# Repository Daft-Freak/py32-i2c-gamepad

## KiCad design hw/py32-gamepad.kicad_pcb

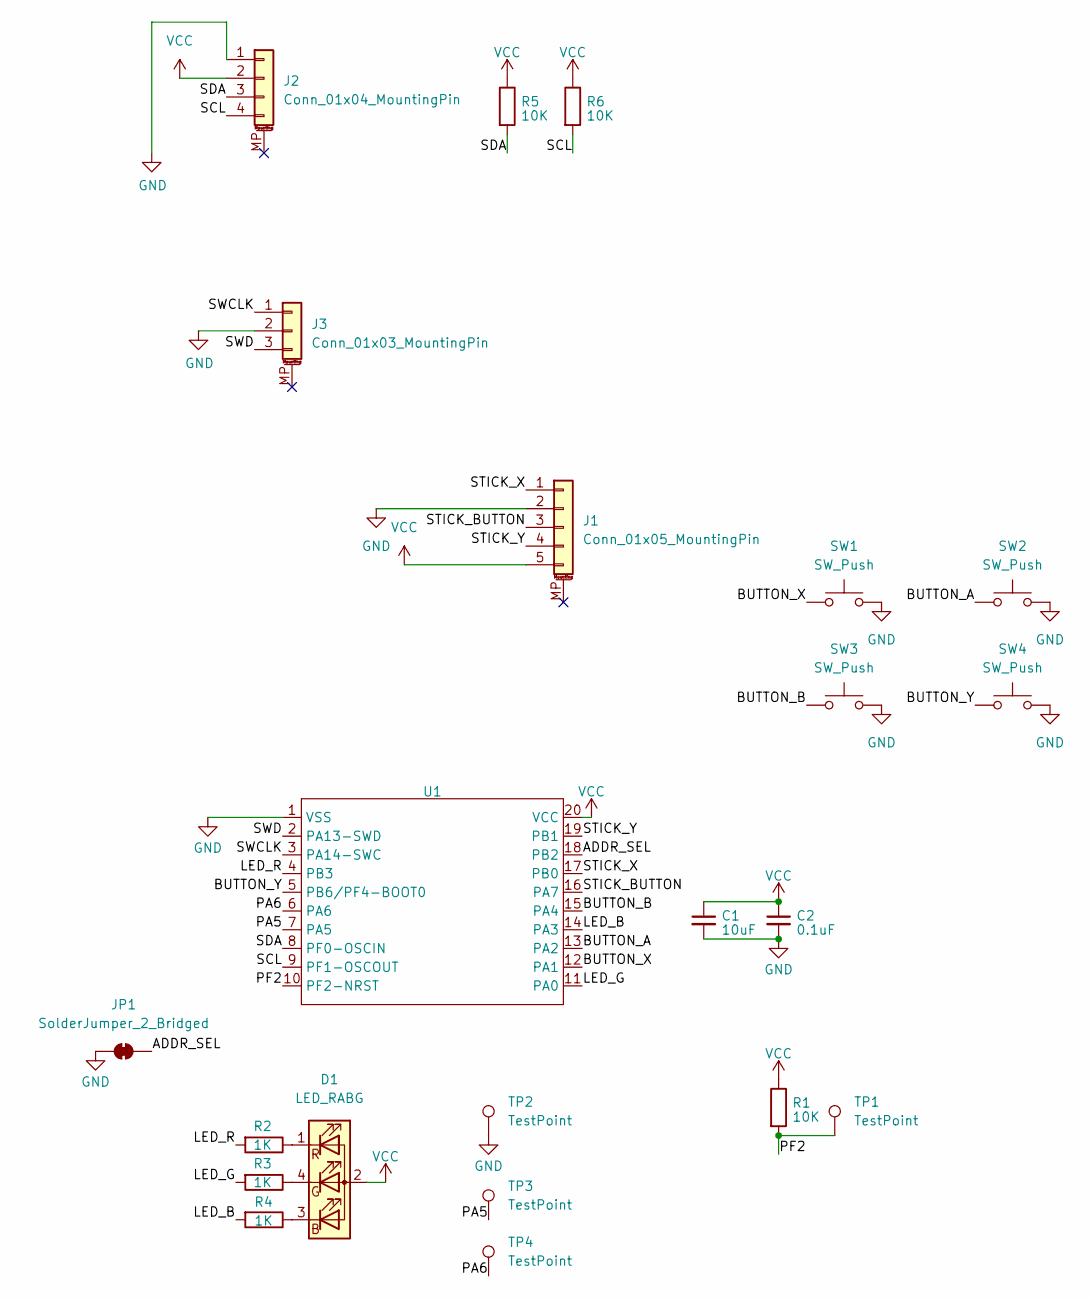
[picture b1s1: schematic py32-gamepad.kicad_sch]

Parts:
C1: 10uF; C_0603_1608Metric
C2: 0.1uF; C_0402_1005Metric
D1: LED_RABG; LED_0606
J1: Conn_01x05_MountingPin; HCTL_HC-FPC-05-09-5RLTAG-00_1x05-1MP_P0.50mm_Horizontal
J2: Conn_01x04_MountingPin; JST_SH_SM04B-SRSS-TB_1x04-1MP_P1.00mm_Horizontal
J3: Conn_01x03_MountingPin; JST_SH_SM03B-SRSS-TB_1x03-1MP_P1.00mm_Horizontal
JP1: SolderJumper_2_Bridged; SolderJumper-2_P1.3mm_Bridged_RoundedPad1.0x1.5mm
R1, R5, R6: 10K; R_0402_1005Metric
R2, R3, R4: 1K; R_0402_1005Metric
SW1, SW2, SW3, SW4: SW_Push; SW_Push_1P1T_NO_GT-TC155x
TP1, TP2, TP3, TP4: TestPoint; TestPoint_Pad_1.0x1.0mm
U1: TSSOP-20_4.4x6.5mm_P0.65mm

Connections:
/ADDR_SEL: JP1.2 (B), U1.18 (PB2)
/BUTTON_A: SW2.1, U1.13 (PA2)
/BUTTON_B: SW3.1, U1.15 (PA4)
/BUTTON_X: SW1.1, U1.12 (PA1)
/BUTTON_Y: SW4.1, U1.5 (PB6/PF4-BOOT0)
/LED_B: R4.2, U1.14 (PA3)
/LED_G: R3.2, U1.11 (PA0)
/LED_R: R2.2, U1.4 (PB3)
/PA5: TP3.1, U1.7 (PA5)
/PA6: TP4.1, U1.6 (PA6)
/PF2: R1.2, TP1.1, U1.10 (PF2-NRST)
/SCL: J2.4, R6.2, U1.9 (PF1-OSCOUT)
/SDA: J2.3, R5.2, U1.8 (PF0-OSCIN)
/STICK_BUTTON: J1.3, U1.16 (PA7)
/STICK_X: J1.1, U1.17 (PB0)
/STICK_Y: J1.4, U1.19 (PB1)
/SWCLK: J3.1, U1.3 (PA14-SWC)
/SWD: J3.3, U1.2 (PA13-SWD)
GND: C1.2, C2.2, J1.2, J2.1, J3.2, JP1.1 (A), SW1.2, SW2.2, SW3.2, SW4.2, TP2.1, U1.1 (VSS)
unnamed: D1.3 (BK), R4.1
unnamed: D1.4 (GK), R3.1
unnamed: D1.1 (RK), R2.1
VCC: C1.1, C2.1, D1.2 (A), J1.5, J2.2, R1.1, R5.1, R6.1, U1.20 (VCC)

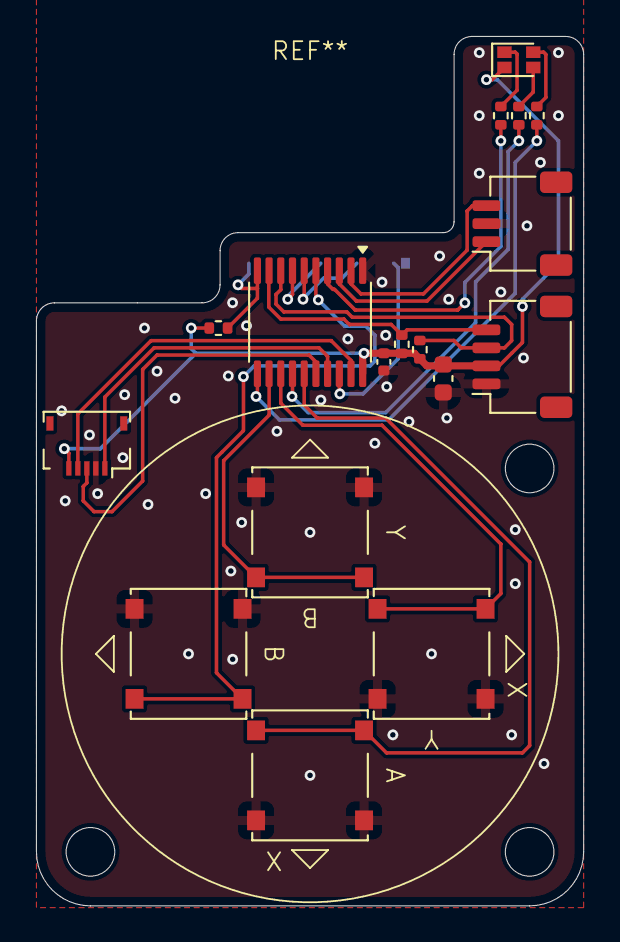
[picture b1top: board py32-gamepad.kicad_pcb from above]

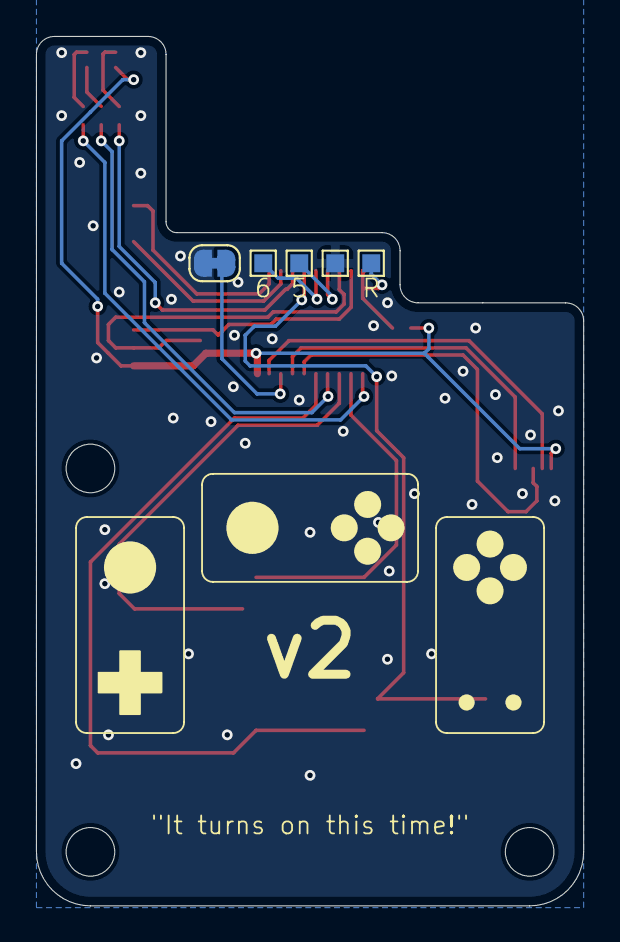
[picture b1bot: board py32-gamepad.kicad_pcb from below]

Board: 2 copper layers, 30.4 x 48.3 mm, 22 parts (5 on the bottom side), 23 nets.

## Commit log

2024-11-14 Initial CMake setup
    It compiles, but we're missing the startup code. startup and linker script taken from https://github.com/IOsetting/py32f0-template
2024-11-14 Import minimal ARM CMSIS headers
    https://github.com/ARM-software/CMSIS_6 v6.1.0
2024-11-14 Import (minimal) puya CMSIC pack
    From https://www.puyasemi.com/uploadfiles/Puya.PY32F0xx_DFP.1.2.2.pack
2024-11-14 Build system init code
2024-11-14 Debug setup
    That was easier than expected
2024-11-14 Setup clocks and test uart
2024-11-15 Init systick and add a very basic delay func
2024-11-15 uart printf helper
2024-11-15 ADC setup
2024-11-15 Less adc printing
2024-11-15 Big pile of gpio helpers
    Also, use the right port for the analog pins
2024-11-15 Some more inputs
2024-11-16 I2C slave setup
    Okay, that's the basic idea working!
2024-12-17 Update for PCB
    Mostly disabling UART and pulling up a few more pins
2024-12-17 Inputs are inputs
2024-12-17 Add a few more GPIO helpers
2024-12-17 Some initial LED PWM
    Because of board mistakes we only have PWM on G, and no R at all
2024-12-19 Enable ADC interrupt and WFE while reading
2024-12-19 SysTick intr and sleepy delay
2024-12-19 I2C address config
2024-12-19 Partial red LED hack on PA5
2024-12-19 Move GPIO helpers to a header
2024-12-19 gpio.h fixes for C
2024-12-19 Refactor UART helpers out of main
2024-12-19 Move global vars together at the top
2024-12-19 LED gamma correction
    Throwing some numbers at it
2024-12-20 Add 16 bytes of I2C writable data
    Should be more than enough
2024-12-20 Control LED from I2C data
2024-12-24 Add delay before reading address sel
2025-01-17 Update for V2
2025-01-22 It's a gamepad
2025-01-22 Add board kicad project
    V2/the working version
2025-01-22 ... forgot the gitignore
2025-01-22 Add some support for calibarion values
    Not persisted yet bbut can be read/written
2025-01-22 Modify linker script to add a section for code in RAM
2025-01-22 Write calibration to the end of flash
2025-01-22 Fix ADC clamping
2025-01-30 Rework I2C a bit and handle bus errors
    This doesn't fully fix the reset problems but does improve it a lot
